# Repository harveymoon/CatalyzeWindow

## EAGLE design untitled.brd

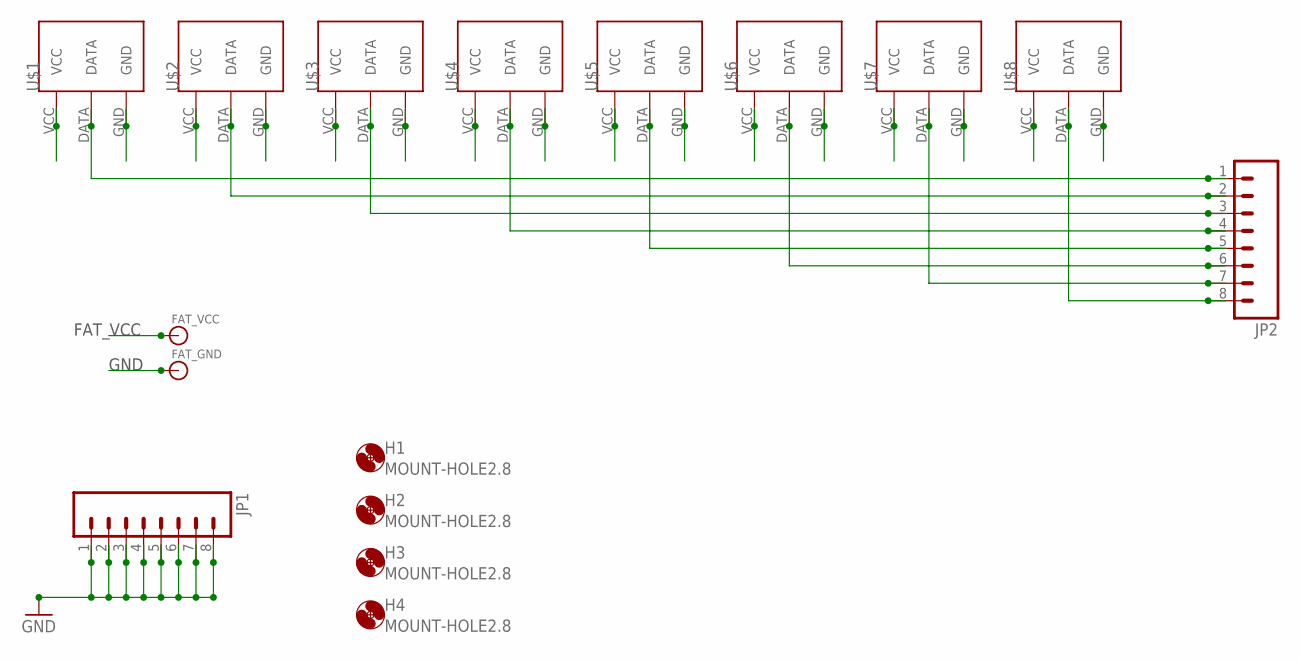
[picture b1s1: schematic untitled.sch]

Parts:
FAT_GND: BANANA_CONN
FAT_VCC: BANANA_CONN
H1, H2, H3, H4: MOUNT-HOLE2.8; 2,8
JP1, JP2: M081X08; 1X08
U$1, U$2, U$3, U$4, U$5, U$6, U$7, U$8: OSTOQ035450

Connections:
FAT_VCC: FAT_VCC.P$1, U$1.VCC, U$2.VCC, U$3.VCC, U$4.VCC, U$5.VCC, U$6.VCC, U$7.VCC, U$8.VCC
GND: FAT_GND.P$1, JP1.1, JP1.2, JP1.3, JP1.4, JP1.5, JP1.6, JP1.7, JP1.8, U$1.GND, U$2.GND, U$3.GND, U$4.GND, U$5.GND, U$6.GND, U$7.GND, U$8.GND
unnamed: JP2.1, U$1.DATA
unnamed: JP2.2, U$2.DATA
unnamed: JP2.3, U$3.DATA
unnamed: JP2.4, U$4.DATA
unnamed: JP2.5, U$5.DATA
unnamed: JP2.6, U$6.DATA
unnamed: JP2.7, U$7.DATA
unnamed: JP2.8, U$8.DATA

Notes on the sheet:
GND
FAT_VCC

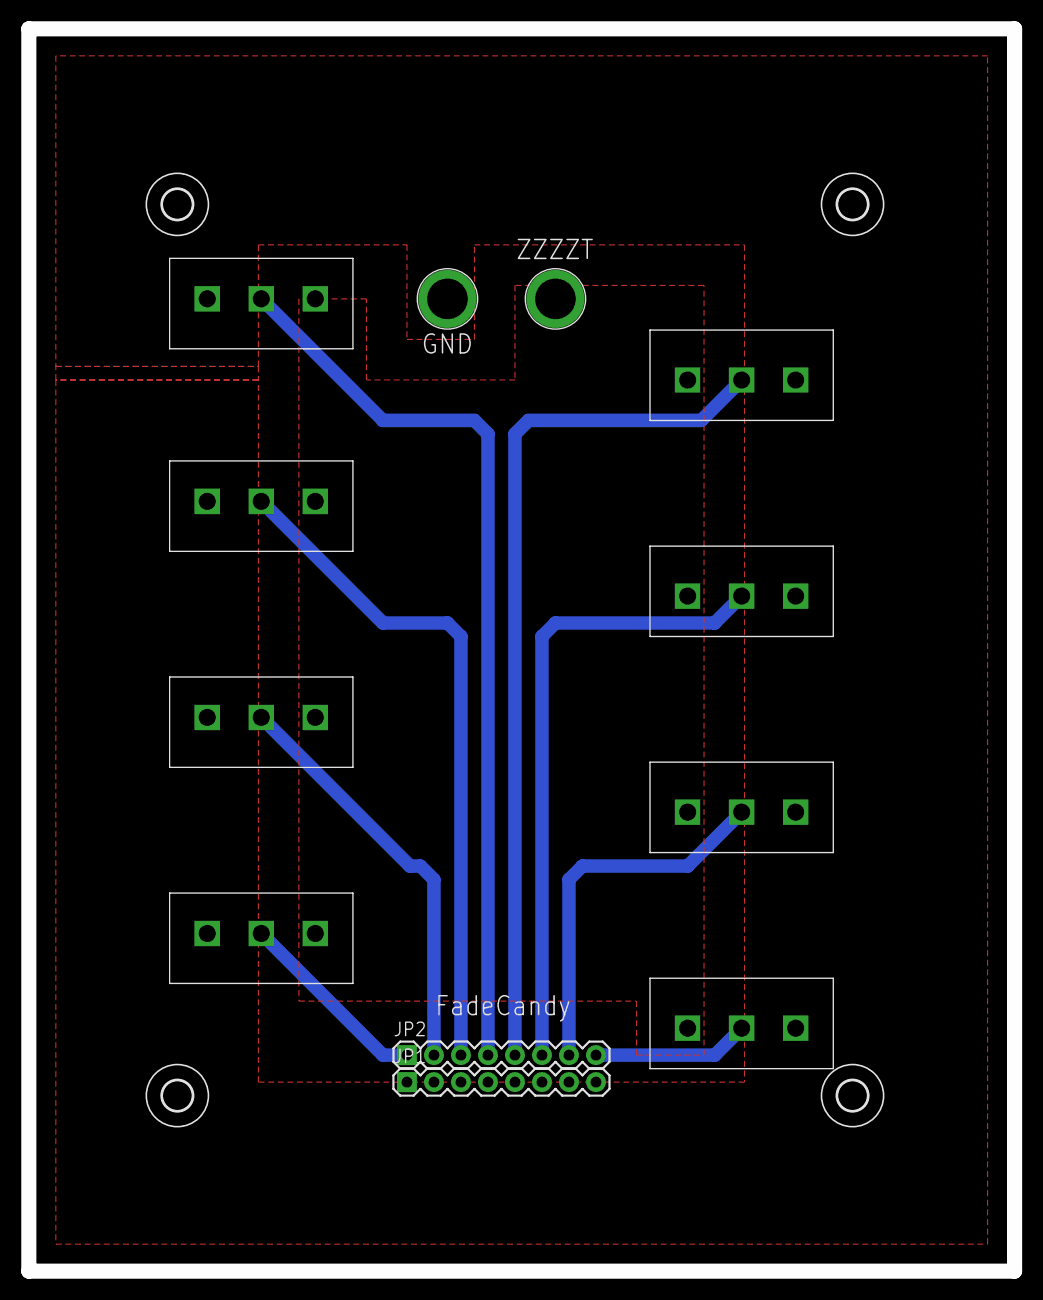
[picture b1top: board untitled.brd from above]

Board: 2 copper layers, 92.7 x 116.8 mm, 16 parts (0 on the bottom side), 10 nets.

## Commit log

2014-11-24 Added processing files and server config
2014-11-24 Uploading data and images for the text playback system. Uses images on a per-pixel input. input image is size (n,6px) where n is as long as you want it to be.

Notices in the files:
parts and their libraries:
SparkFun-Connectors: Licensing: CC v3.0 Share-Alike You are welcome to use this library for commercial purposes.
